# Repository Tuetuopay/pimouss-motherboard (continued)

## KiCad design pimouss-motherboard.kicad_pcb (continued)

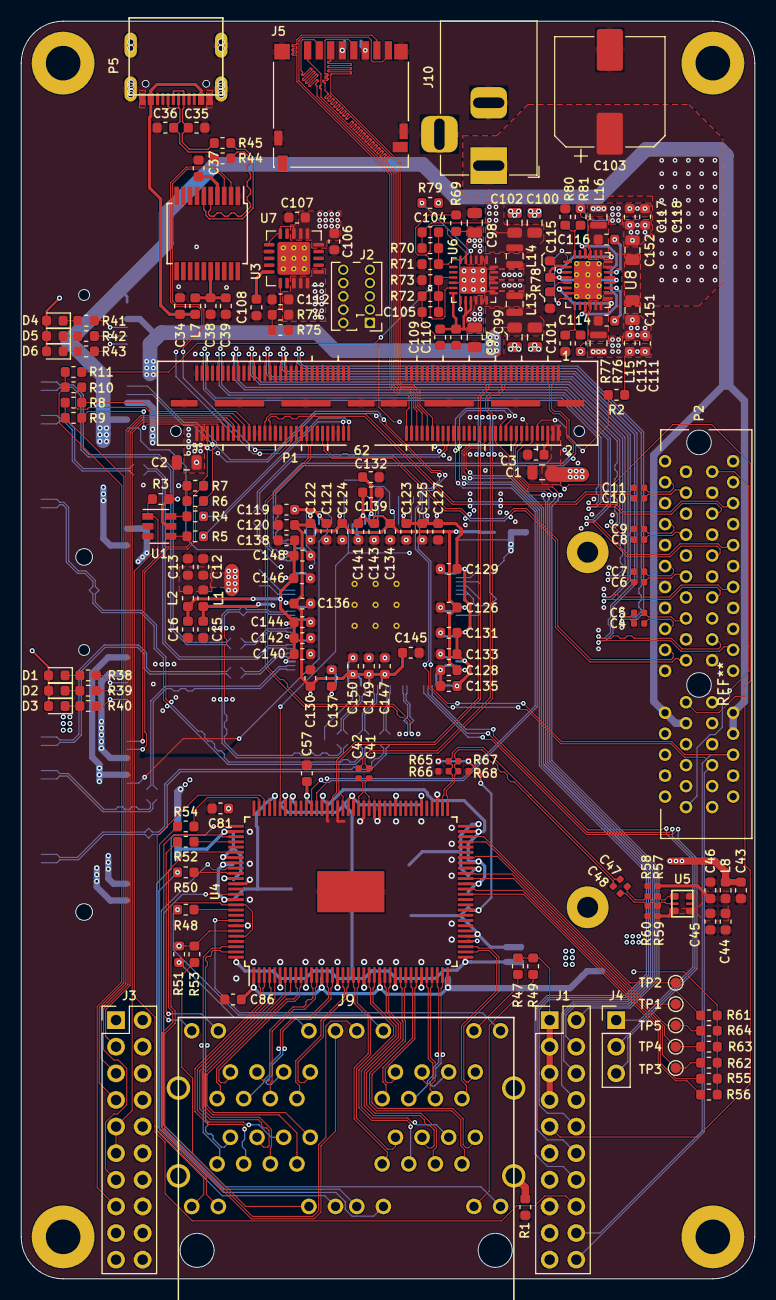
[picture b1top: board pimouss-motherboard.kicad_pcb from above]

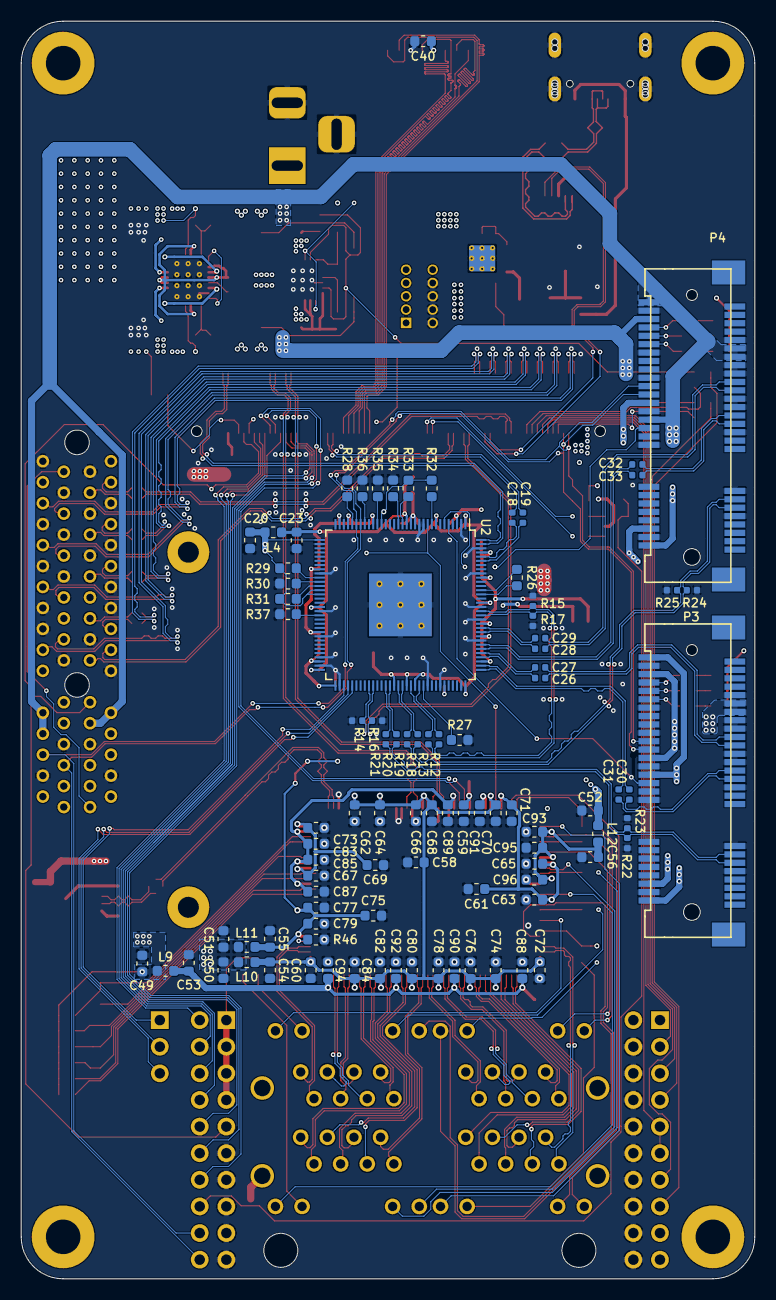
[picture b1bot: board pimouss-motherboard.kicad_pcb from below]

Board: 4 copper layers, 70.0 x 120.0 mm, 271 parts (93 on the bottom side), 241 nets.

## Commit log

2019-03-19 Fix absolute paths issues
2019-03-20 Add gitignore
2019-03-20 lib: Add power rail symbols
2019-03-20 lib: Fix some 88E1545 pin placements
2019-03-20 lib: Add CH340C IC
2019-03-20 lib: Add SN74AUC1G19 IC
2019-03-20 sch: Done PHY power supplies
2019-03-20 sch: Done phy data plane
2019-03-20 sch: Done PHY control plane
2019-03-20 sch: USB-Serial console done
2019-03-20 sch: Pimouss connector done
2019-03-20 sch: Plug PHY signals and misc cosmetic changes
2019-03-22 lib: Add X1 and X4 PCIe connectors
2019-03-23 sch: Add PCIe connectors
2019-03-23 lib: Add 3D shape for PCIe x4 connector
2019-03-23 lib: Add 3D model for mini pcie socket
2019-03-23 lib: Move 3D models to dedicated folder
2019-03-23 lib: Transition 3D models from IGS to STEP
2019-03-23 sch: Add micro SD
2019-03-23 sch: Add PCIe power supply
2019-03-23 lib: Add LTC3633
2019-03-23 sch: Add 5V PSU
2019-03-23 sch: Add main power input
2019-03-23 lib: Add 89HPES4T4 PCIe switch
2019-03-23 lib: Add PI7C9X2G404SL PCIe switch
2019-03-23 sch: Misc fixes
2019-03-24 sch: Add second mPCIe port with PCIe switch
2019-03-24 lib: Add TMS-105-57-G-D connector
2019-03-24 sch: Add some PCIe doc and termination resistors
2019-03-24 sch: Add pimouss power connector
2019-03-24 sch: Swap mPCIe 1 and swtich sheets
2019-03-24 sch, lib: Upgrade to KiCAD 5.1.0
2019-03-24 lib: Add close enough 3D model for USB C connector
2019-03-24 sch: Add connectors for JTAG and GPIO
2019-03-25 sch: Renumber properly sheets
2019-03-25 sch: Set DC input cap value
2019-03-25 sch, lib: Add 1V rail with TPS74401 LDO
2019-03-25 sch: Add misc doc texts
2019-03-26 sch: Move PHY blocks to main page
2019-03-26 sch: Better PCIe clock terminations
2019-03-27 sch: Replace regular symbols with small variant
    Done for most capacitors and resistors
2019-03-29 sch: Misc fixes
    - add missing NC on PCIe switch
    - fix incorrect cap values on PCIe supply
    - fix main schematic interco labels
    - fix PHY JTAG signal name
2019-03-29 sch: Add PCIe switch clocks documentation
2019-03-30 sch: Remove ALL busses since kicad's support is broken
2019-03-30 lib: Tweak some component outputs to make ERC happy
2019-03-30 sch: Make ERC happy with dummy power outputs
2019-03-30 lib, sch: Misc changes to make ERC happy
    - add resistors to PCIe switch GPIOs
    - add NC flags on PHY unused LED outputs
    - add dummy supply on Earth PSU
    - add dummy supply on PHY ref clock's VCC
    - LTC3633: deduplicate SW1/2 outputs
    - ILS8033: deduplicate LX1/2 and PGND1/2 outputs
2019-03-30 lib: Move mPCIe socket to local lib
2019-04-01 lib: Add footprint+3d for Vishay IHHP
2019-04-01 Add fp-info-cache to gitignore
2019-04-01 sch: Annotate & associate symbols with footprints
2019-04-02 sch: Fix PHY ref clk footprint
2019-04-02 lib, sch: Fix connectors refdes letter
2019-04-02 sch: Add missing differential net names
2019-04-03 pro: Setup PCB stackup and DRC
2019-04-03 lib: dos2unix pass
2019-04-03 lib: Fix footprints texts sizes
2019-04-03 sch: Change PCIe series resistors to 33 ohm
2019-04-04 sch: Add names to ALL PCIe nets
2019-04-08 sch: Change PHY decoupling caps from 100u to 100n
2019-04-10 sch: Fix typo in PCIe net names
2019-04-10 sch: Add missing decoupling caps for PCIe switch
2019-04-12 lib: Fix PHY footprint
2019-04-12 pcb: PCIe SW and PHY decoupling caps done
2019-04-22 pcb: PCIe buck mostly done
2019-04-22 lib: Fix LTC3633 pinout
2019-04-22 sch/power: Add main 5V buck input decoupling caps
2019-04-22 sch: Fixup LTC3633 pinout (cache update)
2019-04-22 lib: Remove LTC3633 stupid bottom layer thermal pad
2019-04-22 pcb: Done main 12v->5v buck
2019-04-22 lib: Add JSAE-5x8 RJ-45 connector footprint
2019-04-23 lib: Add RJSAE-5x8 symbol
2019-04-23 lib/RJSAE-5x8: Swap ports B and C
2019-04-23 lib/RJSAE: Fix footprint pins for port B and D
2019-04-24 sch: Swap individual RJ45 with RJSAE connector
2019-04-24 pcb: Group PSUs and (badly) route RJ45 connector
2019-04-25 pcb: Put RJ jacks closer to PHY and wire PHY LEDs
2019-04-25 pcb: Tune RJ45 diff lanes
2019-04-27 pcb: Rework PCIe X4 connector fanout
2019-04-27 pcb: Add PCIe switch power wiring
2019-04-28 pcb: PHY PSU wiring done
2019-04-30 lib: Add pimouss SoM symbol, footprint and 3D model
    The footprint is not a real one. It is mostly there to house the 3D
    model and placement holes positions
2019-05-03 sch, master: Add pimouss SoM component
2019-05-04 sch: Simplify PSU
2019-05-04 Add several 3D models w/ footprints
    - Barrel Jack 3D model
    - Mini PCIe card
    - PCIe 4X card
2019-05-04 lib: Fix RJ45 block holes
2019-05-04 lib: Fix mini-pcie footprint
    remove dumb silkscreen squares along it...
2019-05-04 lib: Add simple plated hole footprint
    used as mounting hole
2019-05-04 pcb: Place all components on the board
    only routing left...
2019-05-05 sch: Swap some PCIe switch pairs for routing reasons
    - Swap clock outputs
    - Swap data polarities
2019-05-05 pcb: Routed PCIe differential tracks
2019-05-10 pcb: ROUTE ALL THE THINGS
2019-06-01 pcb: Redo all PCIe tracks with smaller tracks and larger clearance
2019-06-01 *: Fix CH430C footprint
2019-06-01 *: Fix TPS74401 thermal pad on bottom layer
2019-06-09 pcb: Minor fixes
2019-06-10 pcb: Rewire some PCIe pairs and add more clearances
2019-06-12 pcb: Better clearances
2019-06-12 pcb: Rewire some PCIe for better clearances
2019-06-13 pcb: Get rid of most antennas
2019-06-13 lib: Add scw logo in lib
2019-06-13 pcb: Stitch ground and cosmetic additions
2019-06-18 lib: Finally fix TSM-105 symbol
2019-06-18 pcb: Add more 12V caps
2019-06-19 pcb: Re-tune PCIe pairs
    Place tuning wiggles closer to bends for better integrity
2019-06-19 pcb: Add diff pair skew tuning parameters
2019-06-19 pcb: Fix a via and add OSHW logo
2019-06-19 pcb: Add OSHW logo and some silkscreen
2019-06-19 pcb: Add Rev 1.0 silk
2019-06-25 pcb: Misc PCIe connector stuff
2019-06-26 sch, pcb: Add testpads on lots of signals
2019-06-27 lib, sch, pcb: Use larger footprint for DCS1122
    The 3.2x2.5mm chip is WAY easier to source than the 2.5x2
2019-06-27 pcb: Misc fixes
2019-06-29 lib, sch: Better solder paste layer for the QFP chips
2019-08-25 pro: Fix solder mask minimum width
    Previous wasn't small enough, not putting any between 0.4mm QFPs,
    rendering hand soldering terrible
2019-10-10 sch, pcb: Connect ISL8033 PGND to GND, fix UART
    Pimouss won't boot when its TXD line is pulled up, which the CH340 does.
2019-10-10 *: Fix MDIO and MDC being swapped
2019-10-11 *: Fix TPS74401 BIAS supply voltage
    Somewhere hidden in the datasheed, it is mentioned that
    Vbias >= Vout + 1.62V... Only in two places, and not clearly stated.
2019-10-26 lib: Add FT230XS symbol
2019-11-06 pcb: Change MDIO vias (dunno what changed, ask KiCAD)
2019-11-06 lib: Swap D+/D- and fix symbol size for FT230XS
2019-11-06 sch: Replace CH340C with FT230XS
    CH340 pulls up its RXD line, which makes the pimouss unhappy: nothing
    will get out of the UART port when its TXD line is held high on boot
2019-11-06 fp: Fix fu*** QSH-060-01 footprint
    - Pins were the wrong length
    - Pins were the wrong distance from the center
    - Ground pads were the wrong length
    - Ground pads were the wrong distance and spacing
    - Mounting holes had the wrong spacing
2019-11-07 sch: Remove BSTRAP_H/L test pads
2019-11-07 pcb: Update QSH footprint and reroute nearby traces
2019-11-19 sch, pcb: Replace CH340 with FT230 and add USB host port
2019-11-19 sch: Changed PCIe switch debug header to test pads
2019-11-19 pcb: Change mounting holes and widen debug headers
    - Change mounting holes from 3.3mm to 3.1mm
    - Move mounting holes closer to board outline
    - Move debug headers (CPU JTAG and GPIOs) further away from quad RJ45
2019-11-19 pcb: Move pimouss power connector a bit right
2019-11-19 pcb: Move some test points out of under the pimouss
2019-11-20 pcb: Move OSHW logo to a more visible place
2019-11-23 fp: Add missing corner holes footprint
2019-11-23 fp: Add KUSBX-SL-CS1N14-B USB-C connector
2019-11-23 sym: Add KUSBX-SL-CS1N14-B symbol
2019-11-23 sch, pcb: Replace USB-C connectors with vertical ones
2019-11-23 fp: Fix Texas PVQFN missing a 3D model
2019-11-25 sch, pcb: Replace large JTAG headers with 1.27 ones
2019-12-03 Add Drone CI
2019-12-03 Add kicad bak files to gitignore
2019-12-03 Try to fix ibom s3 upload
2019-12-03 ci: Reduce upload steps by preparing file tree
2019-12-03 ci: Don't keep every commit artifact in S3
2019-12-03 ci: Generate pick-and-place position file
